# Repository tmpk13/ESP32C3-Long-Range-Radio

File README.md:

# ESP32C3-Long-Range-Radio
Long range radio with the ESP32C3

Layer 1  
  
Layer 2  
  
Layer 3  
  
Layer 4  

## SX126x
[SX126x Refrence Designs](https://www.semtech.com/products/wireless-rf/lora-connect/sx1262)
[SX126x Datasheet](https://semtech.my.salesforce.com/sfc/p/#E0000000JelG/a/2R000000HT7B/4cQ1B3JG0iKRo9DGRkjVuxclfwB.3tfSUcGr.S_dPd4)

Reference design shows capacitors but docs say not needed?

## ESP32C3
https://documentation.espressif.com/esp32-c3-mini-1_datasheet_en.pdf

https://www.lcsc.com/datasheet/C470892.pdf

### Notes:
Swapping to PE4259-63 much easier footprint (maybe less heat dissipation?)

Does vbus go from layer 1 to 4 or stay on 1?
Where to add stitching vias?

Swap to 0402 footprint?

# 1st Version

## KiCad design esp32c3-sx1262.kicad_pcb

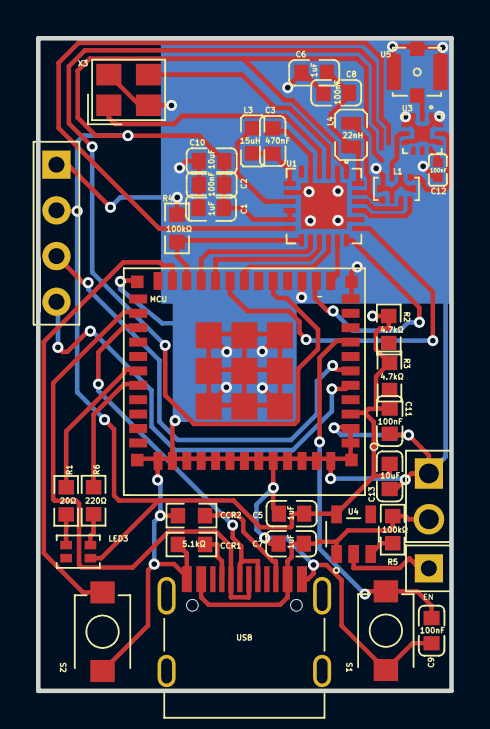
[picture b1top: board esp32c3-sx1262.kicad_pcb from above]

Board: 2 copper layers, 23.0 x 36.3 mm, 36 parts (0 on the bottom side), 37 nets.

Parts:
C1, C5, C6, C7: 1uF; C0603
C2, C8, C9, C11: 100nF; C0603
C3: 470nF; C0603
C10, C13: 10uF; C0603
C12: 100nF; C0402
CCR1, CCR2: 5.1kΩ; R0603
J1: HDR-M-2.54_1x4; HDR-M-2.54_1X4
J3: HDR-M-2.54_1x1; HDR-M-2.54_1X1
J4: HDR-M-2.54_1x2; HDR-M-2.54_1X2
L1: 0900FM15D0039001E; FILTER-SMD_10P-L2.0-W1.3-BL
L3: 15uH; L0603
L4: 22nH; IND-SMD_L1.8-W1.2
LED3: A-SP1963R6GHB1C-C01-3T; LED-SMD_4P-L1.6-W0.8_A-SP1963R6GHB1C-C01-3T
MCU: ESP32-C3-MINI-1U-N4; WIFIM-SMD_61P-L13.2-W12.5-P0.80
R1: 20Ω; R0603
R2, R3: 4.7kΩ; R0603
R4, R5: 100kΩ; R0603
R6: 220Ω; R0603
S1, S2: TS-1088-AR02016; SW-SMD_L3.9-W3.0-P4.45
U1: -; QFN-24_L4.0-W4.0-P0.50-BL-EP2.6
U3: SKY13330-397LF; QFN-12_L2.0-W2.0-P0.50-BL-EP0.8
U4: XC6220B331MR; SOT-23-5_L2.9-W1.6-P0.95-LS2.8-BR
U5: IPEX-1; IPEX-SMD_4P-L2.6-W2.6-LS3.0
USB: HYCW498-USBC16-735B; USB-C-SMD_HYCW498-USBC16-735B
X3: 32MHz; CRYSTAL-SMD_4P-L3.2-W2.5-BL

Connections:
3V3: C1.1, C2.1, C5.1, C10.2, C11.1, C12.2, C13.2, J1.2, LED3.4, MCU.3, R2.2, R3.2, U1.1, U1.10, U1.11, U3.9, U4.5
ANT_SIG: U3.2, U5.4
CCR2_1: CCR2.1, USB.B5
DIO2: U1.12, U3.7
EN: C9.2, MCU.8, S1.1
GND: C1.2, C2.2, C3.1, C5.2, C6.1, C7.2, C8.1, C9.1, C10.1, C11.2, C12.1, C13.1, CCR1.1, CCR2.2, J1.1, J4.1, L1.2, L1.5, L1.7, L1.9, L1.10, MCU.1, MCU.2, MCU.11, MCU.14, MCU.36, MCU.37, MCU.38, MCU.39, MCU.40, MCU.41, MCU.42, MCU.43, MCU.44, MCU.45, MCU.46, MCU.47, MCU.48, MCU.49, MCU.50, MCU.51, MCU.52, MCU.53, MCU.54, MCU.55, MCU.56, MCU.57, MCU.58, MCU.59, MCU.60, MCU.61, R4.1, S1.2, S2.2, U1.2, U1.5, U1.8, U1.20, U1.25, U3.1, U3.3, U3.4, U3.6, U3.10, U3.12, U3.13, U5.1, U5.2, U5.3, USB.A1B12, USB.B1A12, X3.2, X3.4
IO0: MCU.12, U1.17
IO1: MCU.13, U1.18
IO2: J1.4, MCU.5
IO3: J1.3, MCU.6
IO4: MCU.18, U1.16
IO5: MCU.19, U1.19
IO6: MCU.20, U1.15
IO7: MCU.21, U1.14
IO8: MCU.22, R4.2, U1.13
IO9: MCU.23, S2.1
IO10: MCU.16, U3.8
IO20: MCU.30, R1.2
IO21: MCU.31, R6.2
J3_1: J3.1, U4.2
LED3_2: LED3.2, R1.1
LED3_3: LED3.3, R6.1
RFI/RF3: L1.6, U3.11
RFI_N: L1.3, U1.22
RFI_P: L1.4, U1.21
RFO: L1.1, L4.2, U1.23
RFO/RF2: L1.8, U3.5
U1_3: U1.3, X3.3
U1_4: U1.4, X3.1
U1_7: C3.2, L3.1, U1.7
U1_9: L3.2, U1.9
U1_24: C6.2, C8.2, L4.1, U1.24
U4_3: R5.2, U4.3
USB-D+: MCU.27, USB.A6, USB.B6
USB-D-: MCU.26, USB.A7, USB.B7
USB_A5: CCR1.2, USB.A5
VBUS-USB: C7.1, J4.2, R5.1, U4.1, USB.A4B9, USB.B4A9
